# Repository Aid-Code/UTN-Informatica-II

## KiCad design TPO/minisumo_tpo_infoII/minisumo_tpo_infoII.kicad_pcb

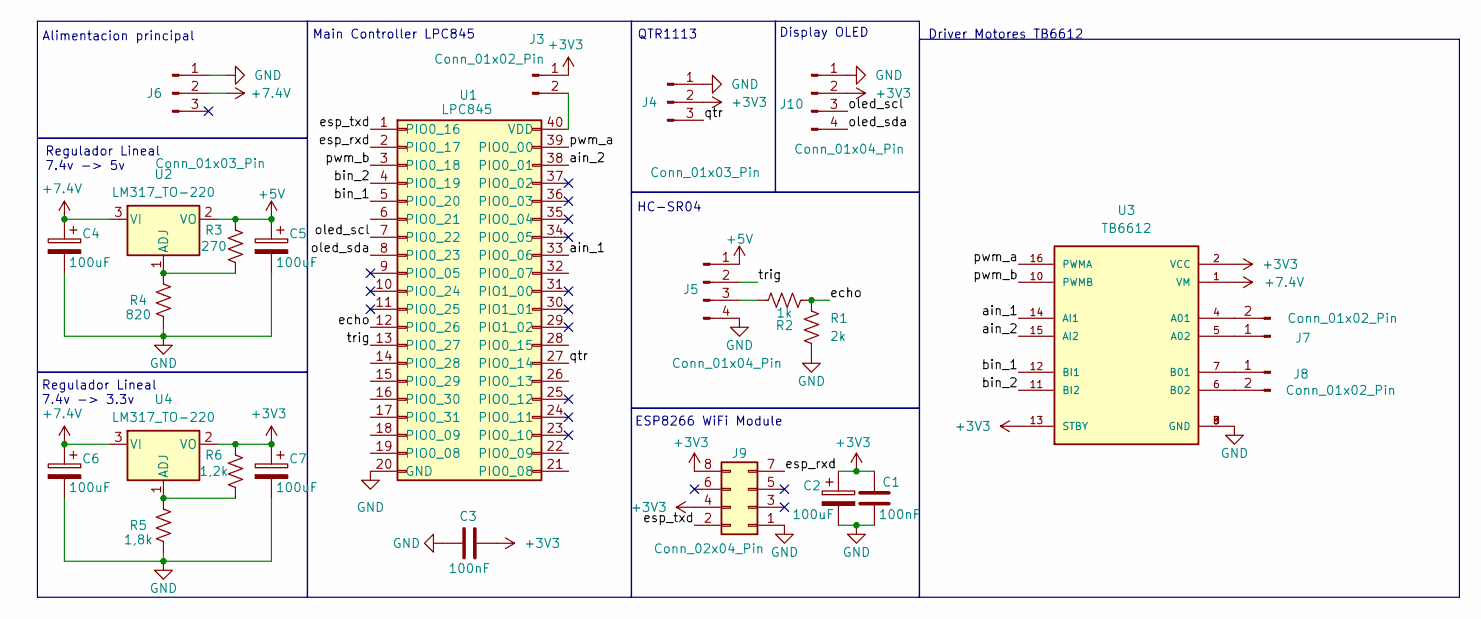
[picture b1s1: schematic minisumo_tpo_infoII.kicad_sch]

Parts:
C1, C3: 100nF; C_Disc_D5.0mm_W2.5mm_P2.50mm
C2, C4, C5, C6, C7: 100uF; CP_Radial_D5.0mm_P2.00mm
J3: Conn_01x02_Pin; PinHeader_1x02_P2.54mm_Vertical
J4, J6: Conn_01x03_Pin; PinHeader_1x03_P2.54mm_Horizontal
J5: Conn_01x04_Pin; PinHeader_1x04_P2.54mm_Horizontal
J7, J8: Conn_01x02_Pin; PinHeader_1x02_P2.54mm_Horizontal
J9: Conn_02x04_Pin; PinSocket_2x04_P2.54mm_Vertical
J10: Conn_01x04_Pin; PinHeader_1x04_P2.54mm_Vertical
R1: 2k; R_Axial_DIN0207_L6.3mm_D2.5mm_P10.16mm_Horizontal
R2: 1k; R_Axial_DIN0207_L6.3mm_D2.5mm_P10.16mm_Horizontal
R3: 270; R_Axial_DIN0207_L6.3mm_D2.5mm_P10.16mm_Horizontal
R4: 820; R_Axial_DIN0207_L6.3mm_D2.5mm_P10.16mm_Horizontal
R5: 1,8k; R_Axial_DIN0207_L6.3mm_D2.5mm_P10.16mm_Horizontal
R6: 1,2k; R_Axial_DIN0207_L6.3mm_D2.5mm_P10.16mm_Horizontal
U1: LPC845; PinHeader_1x20_P2.54mm_Vertical
U2, U4: LM317_TO-220; TO-220-3_Vertical
U3: TB6612; MODULE_TB6612; PARTREV 11-13-17

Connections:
+3V3: C1.1, C2.1, C3.1, C7.1, J3.1, J4.2, J9.4, J9.8, J10.2, R6.1, U3.2 (VCC), U3.13 (STBY), U4.2 (VO)
+5V: C5.1, J5.1, R3.1, U2.2 (VO)
+7.4V: C4.1, C6.1, J6.2, U2.3 (VI), U3.1 (VM), U4.3 (VI)
/ain_1: U1.33 (PIO0_06), U3.14 (AI1)
/ain_2: U1.38 (PIO0_01), U3.15 (AI2)
/bin_1: U1.5 (PIO0_20), U3.12 (BI1)
/bin_2: U1.4 (PIO0_19), U3.11 (BI2)
/echo: R1.1, R2.2, U1.12 (PIO0_26)
/esp_rxd: J9.7, U1.2 (PIO0_17)
/esp_txd: J9.2, U1.1 (PIO0_16)
/oled_scl: J10.3, U1.7 (PIO0_22)
/oled_sda: J10.4, U1.8 (PIO0_23)
/pwm_a: U1.39 (PIO0_00), U3.16 (PWMA)
/pwm_b: U1.3 (PIO0_18), U3.10 (PWMB)
/qtr: J4.3, U1.27 (PIO0_14)
/trig: J5.2, U1.13 (PIO0_27)
GND: C1.2, C2.2, C3.2, C4.2, C5.2, C6.2, C7.2, J4.1, J5.4, J6.1, J9.1, J10.1, R1.2, R4.2, R5.2, U1.20 (GND), U3.3 (GND), U3.8 (GND), U3.9 (GND)
unnamed: J3.2, U1.40 (VDD)
unnamed: J5.3, R2.1
unnamed: J7.1, U3.5 (A02)
unnamed: J7.2, U3.4 (A01)
unnamed: J8.1, U3.7 (B01)
unnamed: J8.2, U3.6 (B02)
unnamed: R3.2, R4.1, U2.1 (ADJ)
unnamed: R5.1, R6.2, U4.1 (ADJ)

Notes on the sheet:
HC-SR04
Driver Motores TB6612
Regulador Lineal 7.4v -> 3.3v
QTR1113
Alimentacion principal
Display OLED
Main Controller LPC845
ESP8266 WiFi Module
Regulador Lineal 7.4v -> 5v

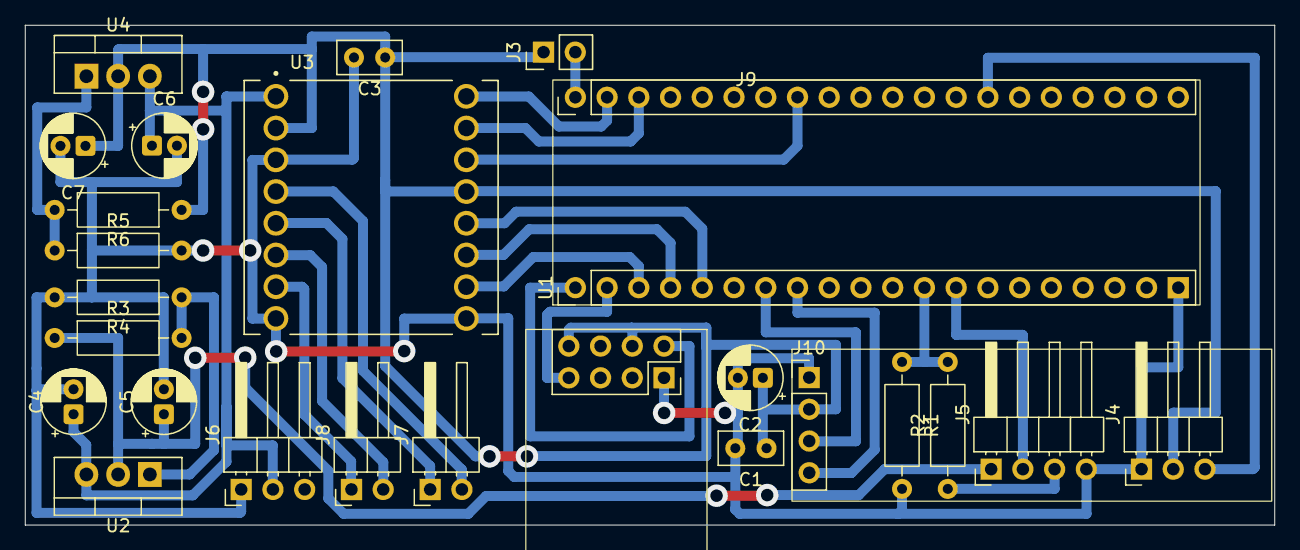
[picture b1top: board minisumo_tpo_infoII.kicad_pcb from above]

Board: 2 copper layers, 100.0 x 40.0 mm, 25 parts (0 on the bottom side), 25 nets.
